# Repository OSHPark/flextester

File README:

Flexible PCB to test batteries (coincell, etc) with LED and resistor.

For the Open Hardware Summit 2020.

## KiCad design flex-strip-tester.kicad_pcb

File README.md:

Flexible PCB to test batteries (coincell, etc) with LED and resistor.

- The LED and resistor footprints are 0603 surface mount
- Current version: [flex-strip-tester-v13.kicad_pcb](https://github.com/OSHPark/flextester/blob/master/flex-strip-tester-v13.kicad_pcb)
- [OSH Park shared project](https://oshpark.com/shared_projects/9d3G335O)
- [Blog post](https://blog.oshpark.com/2021/01/07/flexible-battery-tester/)
- [Video](https://twitter.com/pdp7/status/1274350903223607299)
- [Images](images)

](images/collage.png)

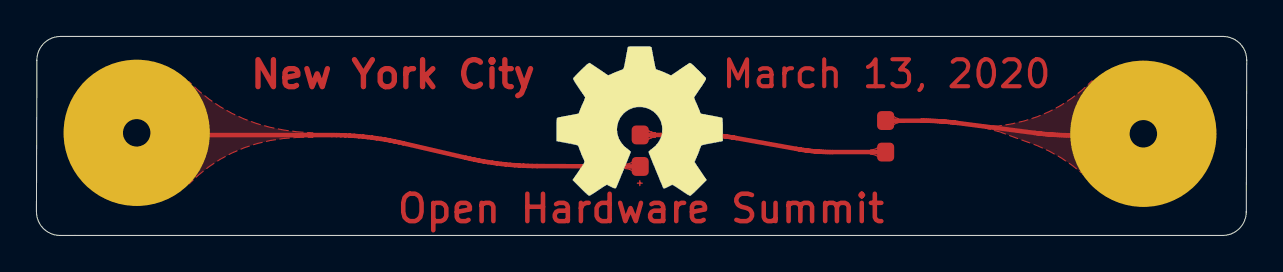
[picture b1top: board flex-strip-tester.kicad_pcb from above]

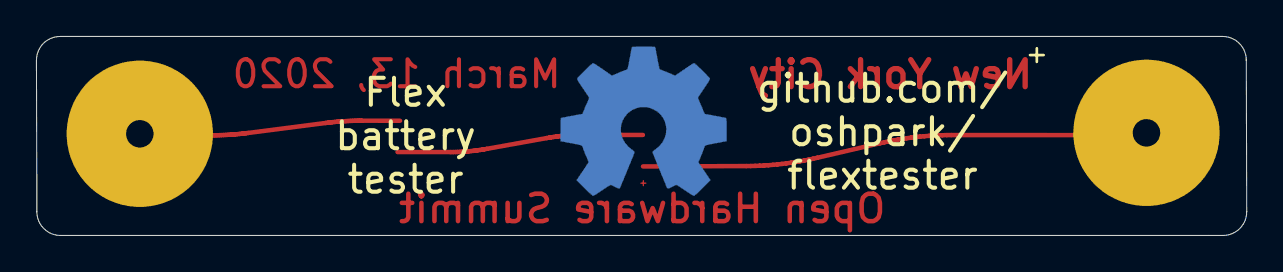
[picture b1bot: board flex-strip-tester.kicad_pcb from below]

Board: 2 copper layers, 67.2 x 11.1 mm, 4 parts (2 on the bottom side), 3 nets.

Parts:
D1: LED; LED_0603_1608Metric_Pad1.05x0.95mm_HandSolder
J1, J2: Conn_01x01_Female; TestPoint_Pad_4.0x4.0mm
R1: R; R_0603_1608Metric_Pad1.05x0.95mm_HandSolder

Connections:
+3V3: D1.2, J1.1
GND: J2.1, R1.1
unnamed: D1.1, R1.2

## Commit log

2020-03-04 add README
2020-03-04 add design for OHS20
2020-03-06 add images
2020-03-11 move resistor to prevent mechanical stress
2020-03-12 add new versions
2020-03-19 try cutout design
2020-03-19 add two LEDs so ligths regardless of polarity
2020-05-22 add v8 of flex tester with two LEDs
2020-06-07 remove resistor
2020-06-12 update designs
    update design with fixes for v8 to add via, and 2 LED design in v9
    also, remove gerbers as not necessary
2020-06-12 update ignore for gerbers
2020-06-15 refactor the v9 design
2020-06-19 new version to fab
2020-06-21 rework cutout and add oshw logo to center
2020-06-28 update flextester
2020-07-10 add new version with LED on both sides
2020-09-07 add v10 which is being order from oshpark flex
2020-12-05 add new version v11 for AA/AAA battery
2020-12-21 osh park freebie version to fab
2020-12-21 update silkscreen layer names for plot
2021-01-07 add the latest flexible LED tester design
2021-01-07 update images
2021-01-07 add collage image
2021-01-08 add new images of LED lit by coincell
2021-01-08 add v14
2021-01-08 update v14
